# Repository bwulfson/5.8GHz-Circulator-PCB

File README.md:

# 5.8GHz Reflection Amplifier
This repo is used to store KiCAD schematics, simulations, and documentation regarding the 5.8GHz Circuit for the Team 15 Reflection Amplifier Project

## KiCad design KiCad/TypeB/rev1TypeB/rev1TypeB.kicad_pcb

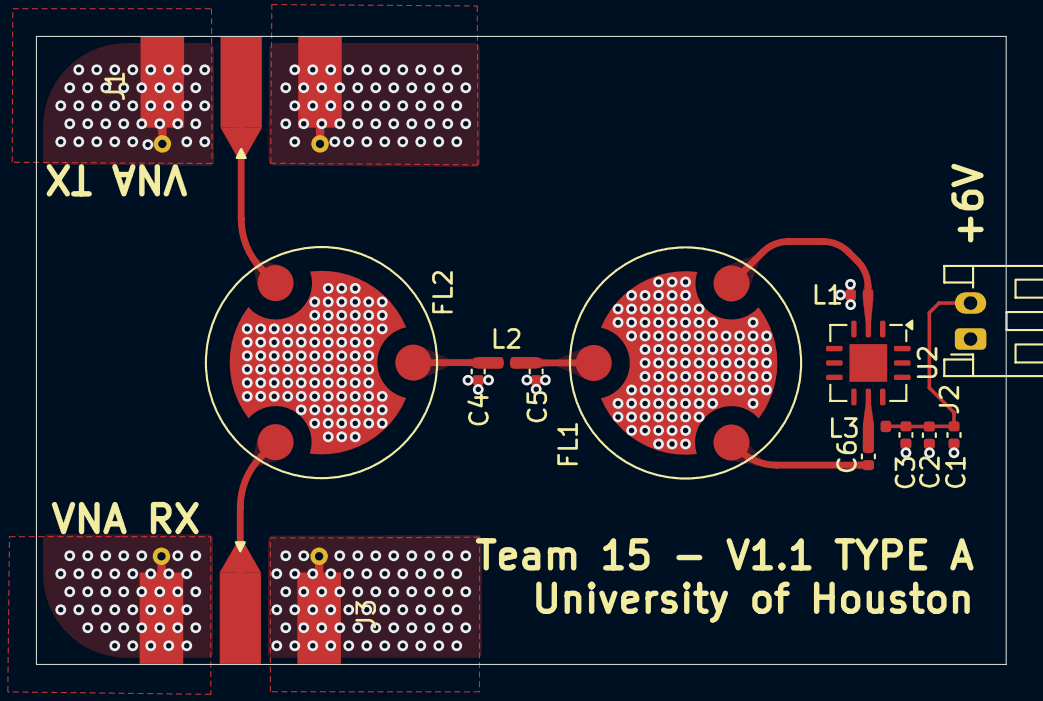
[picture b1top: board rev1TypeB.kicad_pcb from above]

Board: 4 copper layers, 53.9 x 34.9 mm, 15 parts (0 on the bottom side), 9 nets.

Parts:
C1, C2, C3, C4, C5, C6: C; C_0402_1005Metric
FL1, FL2: Circulator_Right_3Port; 5.8GHz_Circulator_Molex
J1, J3: Conn_Coaxial; SMA_Molex_73251-1153_EdgeMount_Horizontal
J2: Conn_01x02; JST_PH_S2B-PH-K_1x02_P2.00mm_Horizontal
L1, L2, L3: L; L_0402_1005Metric
U2: PMA3-83LN+; VQFN-12-1EP_4x4mm_P0.8mm_EP2.1x2.1mm

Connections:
GND: C1.2, C2.2, C3.2, C4.2, C5.2, FL1.4 (GND), FL2.4 (GND), J1.2 (Ext), J2.1, J3.2 (Ext), L1.2, U2.13 (GND)
unnamed: C5.1, FL1.1, L2.2
unnamed: FL1.2, L1.1, U2.2 (RF_IN)
unnamed: C6.2, FL1.3
unnamed: C4.1, FL2.1, L2.1
unnamed: FL2.2, J3.1 (In)
unnamed: FL2.3, J1.1 (In)
unnamed: C1.1, C2.1, C3.1, J2.2, L3.2
unnamed: C6.1, L3.1, U2.8 (RF_OUT_DC_IN)

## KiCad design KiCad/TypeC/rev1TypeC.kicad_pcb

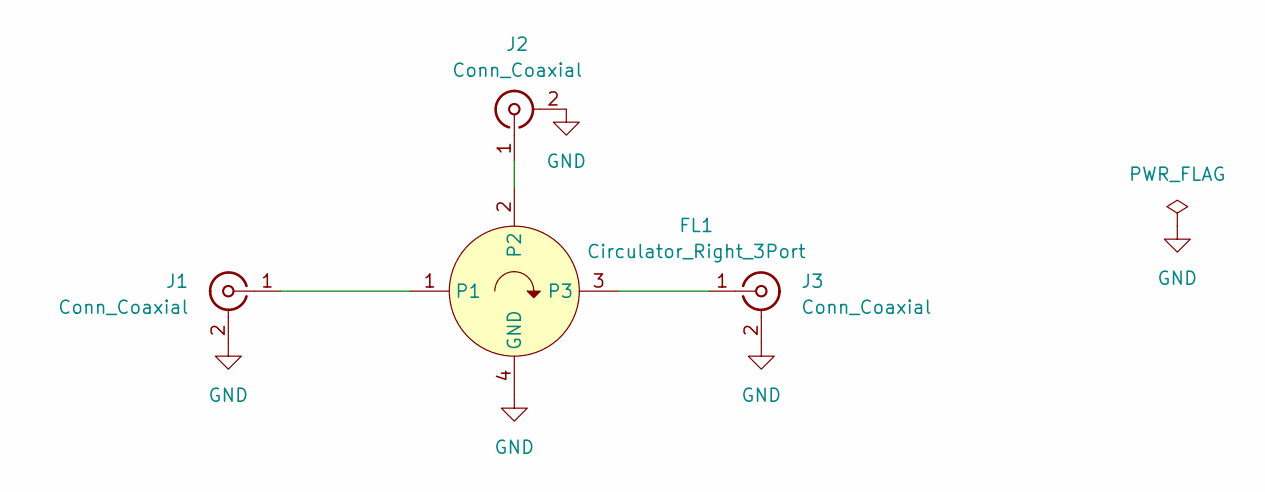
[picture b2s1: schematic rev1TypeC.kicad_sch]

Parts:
FL1: Circulator_Right_3Port; 5.8GHz_Circulator_Molex
J1, J2, J3: Conn_Coaxial; SMA_Molex_73251-1153_EdgeMount_Horizontal

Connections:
GND: FL1.4 (GND), J1.2 (Ext), J2.2 (Ext), J3.2 (Ext)
unnamed: FL1.1, J1.1 (In)
unnamed: FL1.2, J2.1 (In)
unnamed: FL1.3, J3.1 (In)

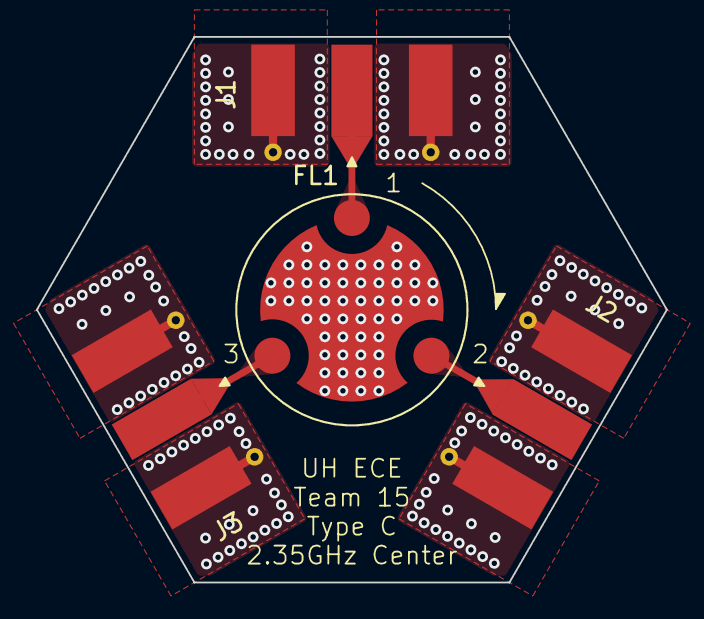
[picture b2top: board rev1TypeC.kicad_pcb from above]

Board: 2 copper layers, 35.0 x 30.3 mm, 4 parts (0 on the bottom side), 4 nets.

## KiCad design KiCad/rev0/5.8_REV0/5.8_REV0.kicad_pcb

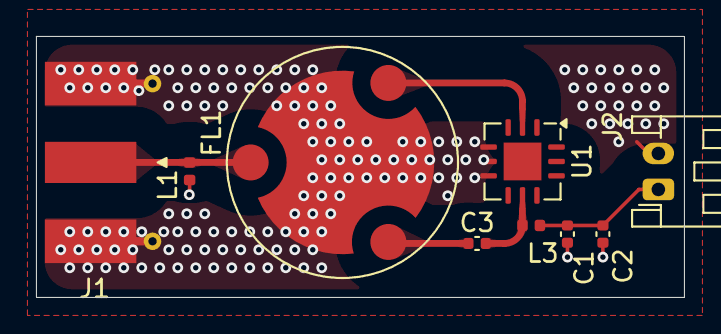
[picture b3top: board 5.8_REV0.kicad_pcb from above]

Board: 4 copper layers, 36.0 x 14.5 mm, 9 parts (0 on the bottom side), 6 nets.

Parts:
C1, C3: 0.01uF; C_0402_1005Metric
C2: 10pF; C_0402_1005Metric
FL1: Circulator_Right_3Port; 5.8GHz_Circulator_Molex
J1: Conn_Coaxial; SMA_Molex_73251-1153_EdgeMount_Horizontal
J2: Conn_01x02; JST_PH_S2B-PH-K_1x02_P2.00mm_Horizontal
L1: 18nH; L_0402_1005Metric
L3: 39nH; L_0402_1005Metric
U1: PMA3-83LN+; VQFN-12-1EP_4x4mm_P0.8mm_EP2.1x2.1mm

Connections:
GND: C1.2, C2.2, FL1.4 (GND), J1.2 (Ext), J2.2, L1.2, U1.1 (NC), U1.3 (NC), U1.4 (NC), U1.5 (NC), U1.6 (NC), U1.7 (NC), U1.9 (NC), U1.12 (NC), U1.13 (GND)
unnamed: FL1.1, J1.1 (In), L1.1
unnamed: FL1.2, U1.2 (RF_IN)
unnamed: C3.1, FL1.3
unnamed: C1.1, C2.1, J2.1, L3.1
unnamed: C3.2, L3.2, U1.8 (RF_OUT_DC_IN)
